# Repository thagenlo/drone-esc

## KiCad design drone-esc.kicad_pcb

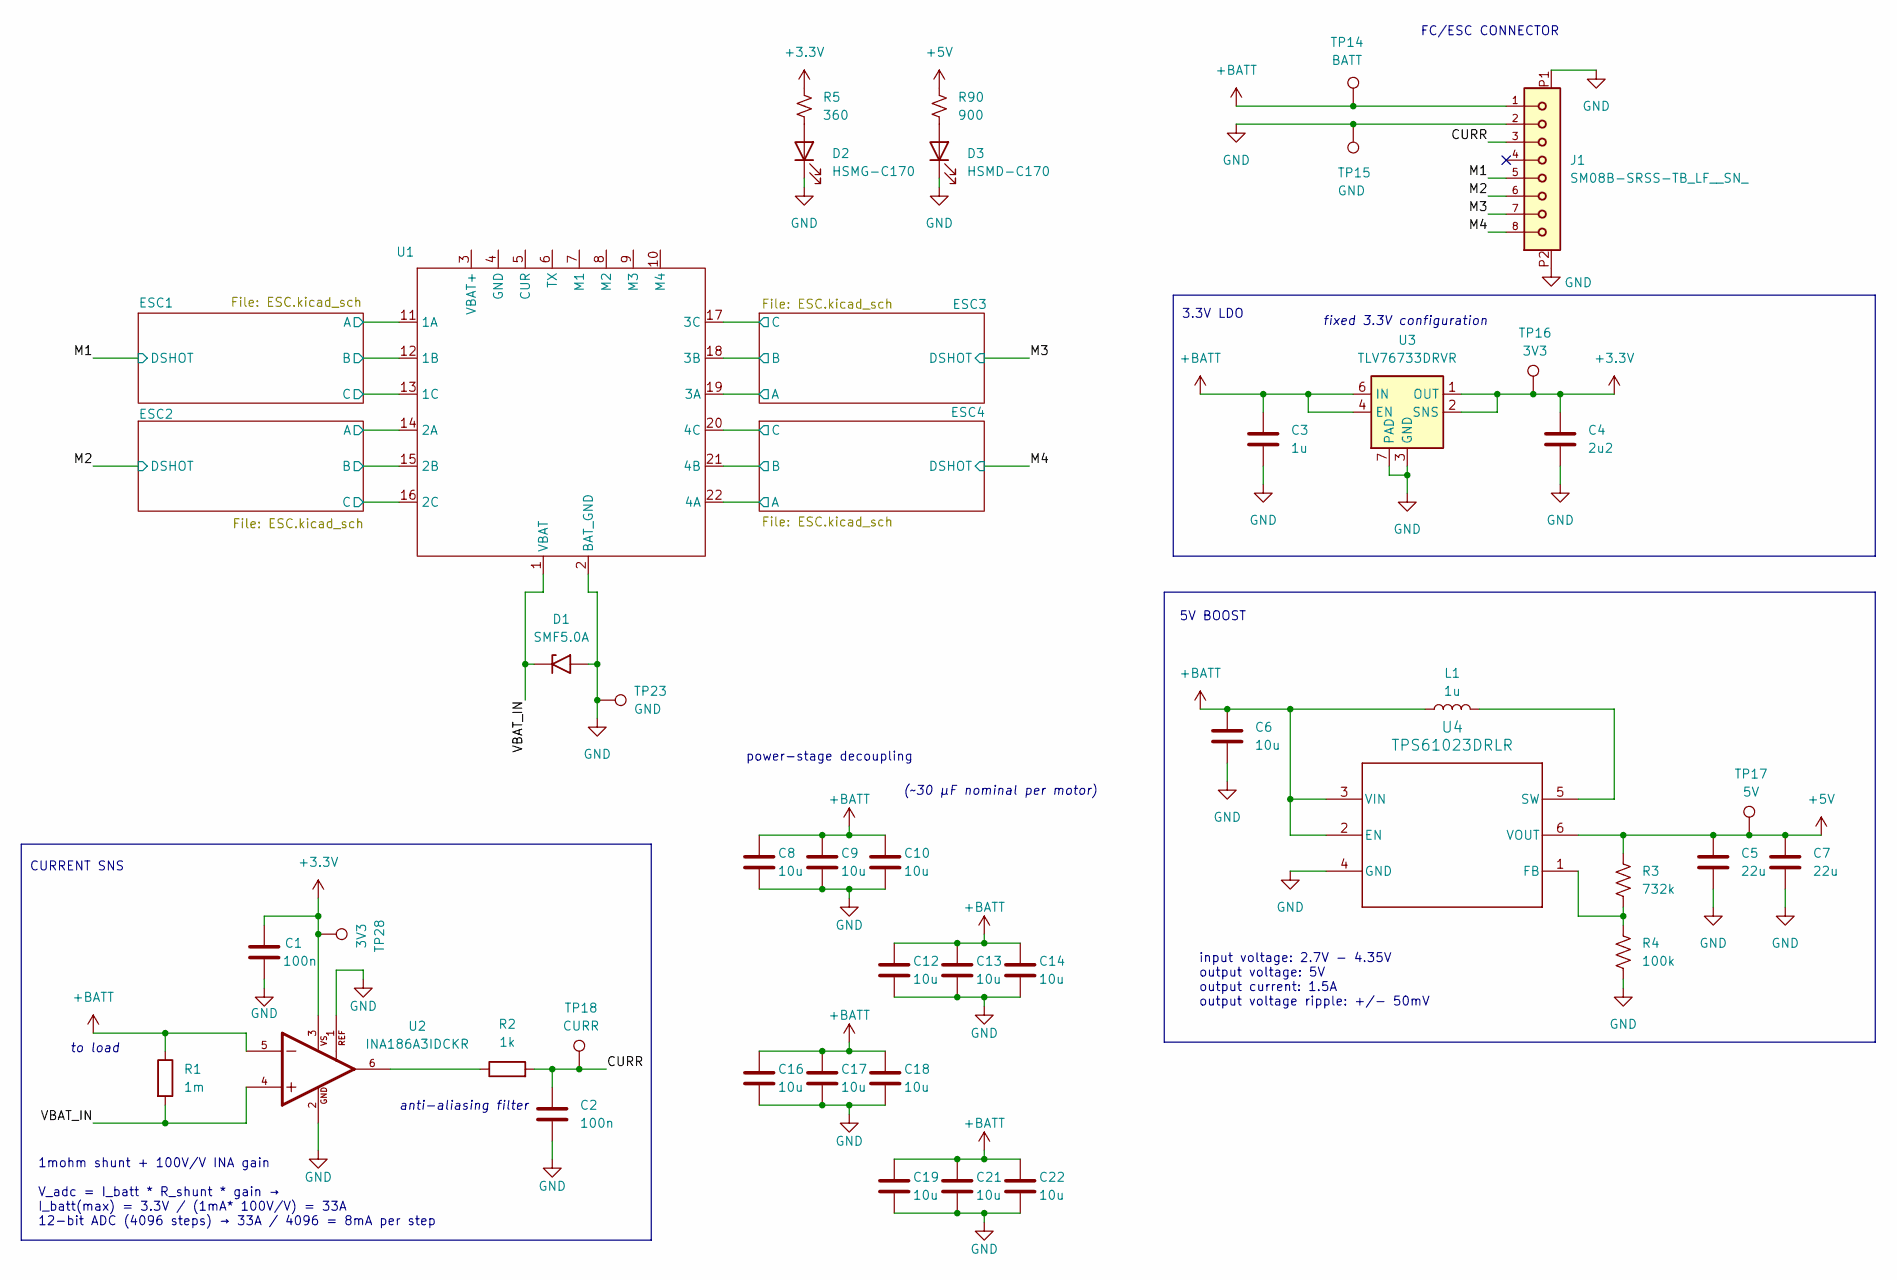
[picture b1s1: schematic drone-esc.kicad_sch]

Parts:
C1, C2: 100n; C_0201_0603Metric
C3: 1u; C_0201_0603Metric
C4: 2u2; C_0201_0603Metric
C5, C7: 22u; C_0201_0603Metric
C6: 10u; C_0201_0603Metric
C8, C9, C10, C12, C13, C14, C16, C17, C18, C19, C21, C22: 10u; C_0805_2012Metric
D1: SMF5.0A; D_SOD-123F
D2: HSMG-C170; LED_0805_2012Metric
D3: HSMD-C170; LED_0805_2012Metric
J1: SM08B-SRSS-TB_LF__SN_; JST_SM08B-SRSS-TB_LF__SN_
L1: 1u; L_0603_1608Metric
R1: 1m; R_2512_6332Metric
R2: 1k; R_0201_0603Metric
R3: 732k; R_0201_0603Metric
R4: 100k; R_0201_0603Metric
R5: 360; R_0201_0603Metric
R90: 900; R_0201_0603Metric
TP14: BATT; TestPoint_Pad_D1.0mm
TP15, TP23: GND; TestPoint_Pad_D1.0mm
TP16, TP28: 3V3; TestPoint_Pad_D1.0mm
TP17: 5V; TestPoint_Pad_D1.0mm
TP18: CURR; TestPoint_Pad_D1.0mm
U1: esc-board
U2: INA186A3IDCKR; SOT65P210X110-6N; PARTREV B
U3: TLV76733DRVR; WSON-6-1EP_2x2mm_P0.65mm_EP1x1.6mm_ThermalVias
U4: TPS61023DRLR; DRL0006A

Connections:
+3.3V: C1.1, C4.1, R5.1, TP16.1 (1_1), TP28.1, U2.3, U3.1 (OUT), U3.2 (SNS); also elsewhere on the board
+5V: C5.1, C7.1, R3.1, R90.1, TP17.1 (1_1), U4.6 (VOUT); also elsewhere on the board
+BATT: C3.1, C6.1, C8.1, C9.1, C10.1, C12.1, C13.1, C14.1, C16.1, C17.1, C18.1, C19.1, C21.1, C22.1, J1.1, L1.1, R1.1, TP14.1, U2.5, U3.4 (EN), U3.6 (IN), U4.2 (EN), U4.3 (VIN); also elsewhere on the board
/CURR: C2.1, J1.3, R2.2, TP18.1 (1_1)
/ESC1/MotorA: U1.11 (1A); also elsewhere on the board
/ESC1/MotorB: U1.12 (1B); also elsewhere on the board
/ESC1/MotorC: U1.13 (1C); also elsewhere on the board
/ESC2/MotorA: U1.14 (2A); also elsewhere on the board
/ESC2/MotorB: U1.15 (2B); also elsewhere on the board
/ESC2/MotorC: U1.16 (2C); also elsewhere on the board
/ESC3/MotorA: U1.19 (3A); also elsewhere on the board
/ESC3/MotorB: U1.18 (3B); also elsewhere on the board
/ESC3/MotorC: U1.17 (3C); also elsewhere on the board
/ESC4/MotorA: U1.22 (4A); also elsewhere on the board
/ESC4/MotorB: U1.21 (4B); also elsewhere on the board
/ESC4/MotorC: U1.20 (4C); also elsewhere on the board
/M1: J1.5; also elsewhere on the board
/M2: J1.6; also elsewhere on the board
/M3: J1.7; also elsewhere on the board
/M4: J1.8; also elsewhere on the board
/VBAT_IN: D1.1 (A1), R1.2, U1.1 (VBAT), U2.4
GND: C1.2, C2.2, C3.2, C4.2, C5.2, C6.2, C7.2, C8.2, C9.2, C10.2, C12.2, C13.2, C14.2, C16.2, C17.2, C18.2, C19.2, C21.2, C22.2, D1.2 (A2), D2.1 (K), D3.1 (K), J1.2, J1.P1, J1.P2, R4.2, TP15.1 (1_1), TP23.1, U1.2 (BAT_GND), U2.1, U2.2, U3.3 (GND), U3.5 (GND), U3.7 (PAD), U4.4 (GND); also elsewhere on the board
unnamed: D2.2 (A), R5.2
unnamed: D3.2 (A), R90.2
unnamed: R2.1, U2.6
unnamed: R3.2, R4.1, U4.1 (FB)
unnamed: L1.2, U4.5 (SW)

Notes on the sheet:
5V BOOST
(~30 µF nominal per motor)
fixed 3.3V configuration
1mohm shunt + 100V/V INA gain V_adc = I_batt * R_shunt * gain → I_batt(max) = 3.3V / (1mA* 100V/V) = 33A 12-bit ADC (4096 steps) → 33A / 4096 = 8mA per step
anti-aliasing filter
FC/ESC CONNECTOR
to load
3.3V LDO
power-stage decoupling
CURRENT SNS
input voltage: 2.7V - 4.35V output voltage: 5V output current: 1.5A output voltage ripple: +/- 50mV

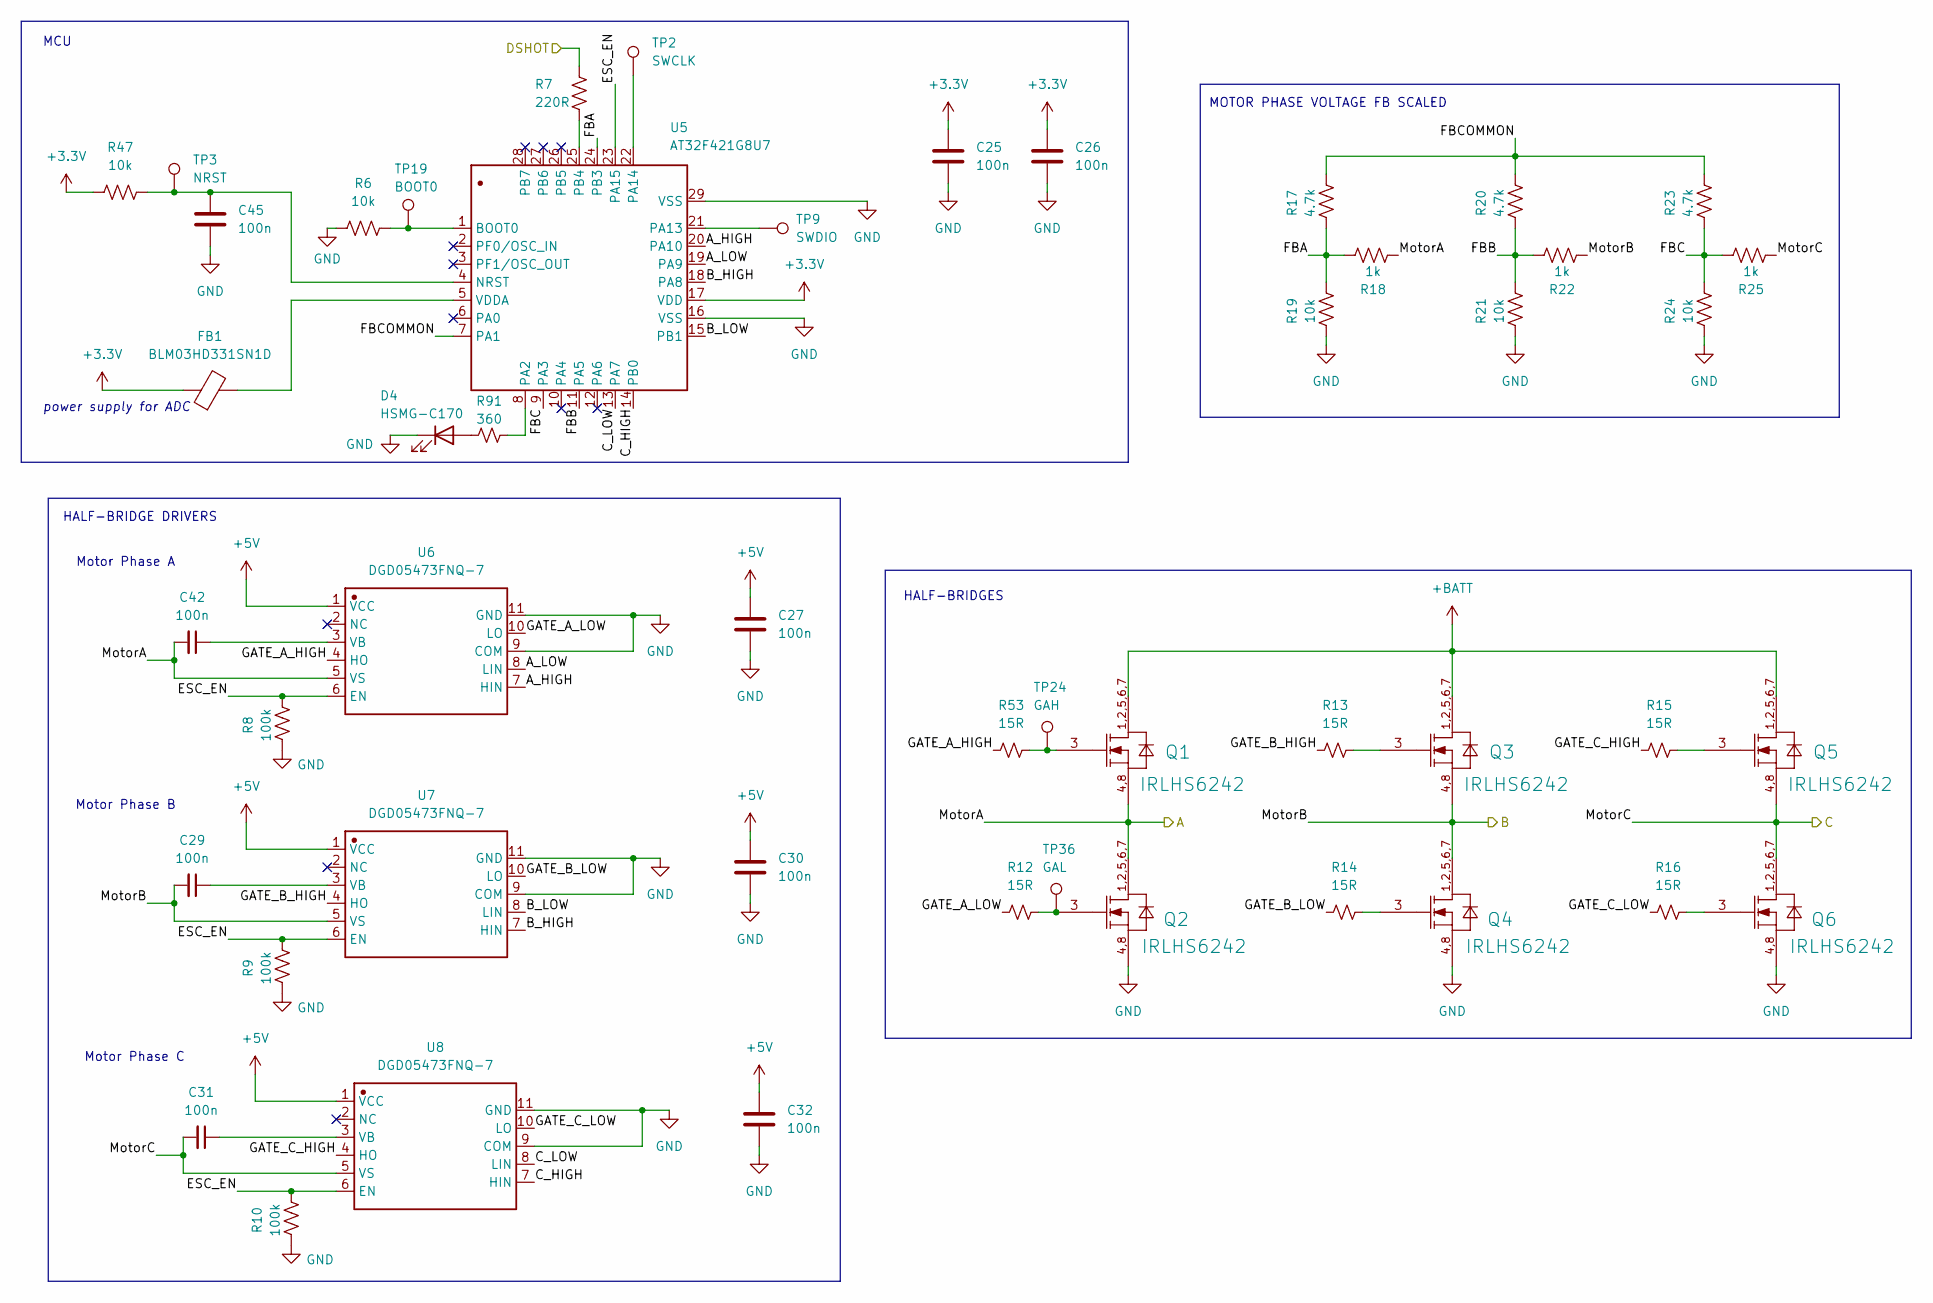
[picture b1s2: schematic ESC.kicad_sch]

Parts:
C25, C26, C27, C29, C30, C31, C32, C42, C45: 100n; C_0201_0603Metric
D4: HSMG-C170; LED_0805_2012Metric
FB1: BLM03HD331SN1D; R_0201_0603Metric
Q1, Q2, Q3, Q4, Q5, Q6: IRLHS6242; IRL100HS121-V
R6, R19, R21, R24, R47: 10k; R_0201_0603Metric
R7: 220R; R_0201_0603Metric
R8, R9, R10: 100k; R_0201_0603Metric
R12, R13, R14, R15, R16, R53: 15R; R_0201_0603Metric
R17, R20, R23: 4.7k; R_0201_0603Metric
R18, R22, R25: 1k; R_0201_0603Metric
R91: 360; R_0201_0603Metric
TP2: SWCLK; TestPoint_Pad_D1.0mm
TP3: NRST; TestPoint_Pad_D1.0mm
TP9: SWDIO; TestPoint_Pad_D1.0mm
TP19: BOOT0; TestPoint_Pad_D1.0mm
TP24: GAH; TestPoint_Pad_D1.0mm
TP36: GAL; TestPoint_Pad_D1.0mm
U5: AT32F421G8U7; QFN-28-1EP_4x4mm_P0.45mm_EP2.4x2.4mm; Manufacturer Part AT32F421G8U7
U6, U7, U8: DGD05473FNQ-7; DFN-10-1EP_3x3mm_P0.5mm_EP1.7x2.5mm; Manufacturer Part DGD05473FNQ-7

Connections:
+3.3V: C25.1, C26.1, FB1.1, R47.1, U5.17 (VDD); also elsewhere on the board
+5V: C27.1, C30.1, C32.1, U6.1 (VCC), U7.1 (VCC), U8.1 (VCC); also elsewhere on the board
+BATT: Q1.1 (DRAIN1), Q1.2 (DRAIN2), Q1.5 (DRAIN3), Q1.6 (DRAIN4), Q1.7 (DRAIN5), Q3.1 (DRAIN1), Q3.2 (DRAIN2), Q3.5 (DRAIN3), Q3.6 (DRAIN4), Q3.7 (DRAIN5), Q5.1 (DRAIN1), Q5.2 (DRAIN2), Q5.5 (DRAIN3), Q5.6 (DRAIN4), Q5.7 (DRAIN5); also elsewhere on the board
/ESC1/A_HIGH: U5.20 (PA10), U6.7 (HIN)
/ESC1/A_LOW: U5.19 (PA9), U6.8 (LIN)
/ESC1/B_HIGH: U5.18 (PA8), U7.7 (HIN)
/ESC1/B_LOW: U5.15 (PB1), U7.8 (LIN)
/ESC1/C_HIGH: U5.14 (PB0), U8.7 (HIN)
/ESC1/C_LOW: U5.13 (PA7), U8.8 (LIN)
/ESC1/ESC_EN: R8.1, R9.1, R10.1, U5.23 (PA15), U6.6 (EN), U7.6 (EN), U8.6 (EN)
/ESC1/FBA: R17.2, R18.1, R19.1, U5.24 (PB3)
/ESC1/FBB: R20.2, R21.1, R22.1, U5.11 (PA5)
/ESC1/FBC: R23.2, R24.1, R25.1, U5.9 (PA3)
/ESC1/FBCOMMON: R17.1, R20.1, R23.1, U5.7 (PA1)
/ESC1/GATE_A_HIGH: R53.1, U6.4 (HO)
/ESC1/GATE_A_LOW: R12.1, U6.10 (LO)
/ESC1/GATE_B_HIGH: R13.1, U7.4 (HO)
/ESC1/GATE_B_LOW: R14.1, U7.10 (LO)
/ESC1/GATE_C_HIGH: R15.1, U8.4 (HO)
/ESC1/GATE_C_LOW: R16.1, U8.10 (LO)
/ESC1/MotorA: C42.2, Q1.4 (SOURCE1), Q1.8 (SOURCE2), Q2.1 (DRAIN1), Q2.2 (DRAIN2), Q2.5 (DRAIN3), Q2.6 (DRAIN4), Q2.7 (DRAIN5), R18.2, U6.5 (VS); also elsewhere on the board
/ESC1/MotorB: C29.2, Q3.4 (SOURCE1), Q3.8 (SOURCE2), Q4.1 (DRAIN1), Q4.2 (DRAIN2), Q4.5 (DRAIN3), Q4.6 (DRAIN4), Q4.7 (DRAIN5), R22.2, U7.5 (VS); also elsewhere on the board
/ESC1/MotorC: C31.2, Q5.4 (SOURCE1), Q5.8 (SOURCE2), Q6.1 (DRAIN1), Q6.2 (DRAIN2), Q6.5 (DRAIN3), Q6.6 (DRAIN4), Q6.7 (DRAIN5), R25.2, U8.5 (VS); also elsewhere on the board
/M1: R7.2; also elsewhere on the board
GND: C25.2, C26.2, C27.2, C30.2, C32.2, C45.2, D4.1 (K), Q2.4 (SOURCE1), Q2.8 (SOURCE2), Q4.4 (SOURCE1), Q4.8 (SOURCE2), Q6.4 (SOURCE1), Q6.8 (SOURCE2), R6.1, R8.2, R9.2, R10.2, R19.2, R21.2, R24.2, U5.16 (VSS), U5.29 (VSS), U6.9 (COM), U6.11 (GND), U7.9 (COM), U7.11 (GND), U8.9 (COM), U8.11 (GND); also elsewhere on the board
unnamed: D4.2 (A), R91.2
unnamed: Q1.3 (GATE), R53.2
unnamed: Q2.3 (GATE), R12.2
unnamed: Q3.3 (GATE), R13.2
unnamed: Q4.3 (GATE), R14.2
unnamed: Q5.3 (GATE), R15.2
unnamed: Q6.3 (GATE), R16.2
unnamed: R6.2, U5.1 (BOOT0)
unnamed: C45.1, R47.2, U5.4 (NRST)
unnamed: R7.1, U5.25 (PB4)
unnamed: FB1.2, U5.5 (VDDA)
unnamed: C42.1, U6.3 (VB)
unnamed: C29.1, U7.3 (VB)
unnamed: C31.1, U8.3 (VB)

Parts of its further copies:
C28, C33, C34, C35, C36, C37, C38, C39, C40, C41, C43, C44, C46, C47, C48, C49, C50, C51, C52, C53, C54, C55, C56, C57, C58, C59, C60: 100n; C_0201_0603Metric
FB2, FB3, FB4: BLM03HD331SN1D; R_0201_0603Metric
Q7, Q8, Q9, Q10, Q11, Q12, Q13, Q14, Q15, Q16, Q17, Q18, Q19, Q20, Q21, Q22, Q23, Q24: IRLHS6242; IRL100HS121-V
R11, R27, R28, R29, R49, R50, R70, R71, R72: 100k; R_0201_0603Metric
R26, R30, R35, R40, R45, R48, R51, R57, R62, R67, R69, R73, R78, R83, R88: 10k; R_0201_0603Metric
R31, R52, R74: 220R; R_0201_0603Metric
R32, R33, R36, R37, R42, R43, R54, R55, R58, R59, R64, R65, R75, R76, R79, R80, R85, R86: 15R; R_0201_0603Metric
R34, R39, R44, R56, R61, R66, R77, R82, R87: 4.7k; R_0201_0603Metric
R38, R41, R46, R60, R63, R68, R81, R84, R89: 1k; R_0201_0603Metric
U9, U10, U11, U13, U14, U15, U17, U18, U19: DGD05473FNQ-7; DFN-10-1EP_3x3mm_P0.5mm_EP1.7x2.5mm; Manufacturer Part DGD05473FNQ-7
U12, U16, U20: AT32F421G8U7; QFN-28-1EP_4x4mm_P0.45mm_EP2.4x2.4mm; Manufacturer Part AT32F421G8U7

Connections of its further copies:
+3.3V: C40.1, C41.1, C50.1, C51.1, C59.1, C60.1, FB2.1, FB3.1, FB4.1, R26.1, R48.1, R69.1, U12.17 (VDD), U16.17 (VDD), U20.17 (VDD); also elsewhere on the board
+5V: C28.1, C37.1, C38.1, C39.1, C48.1, C49.1, C56.1, C57.1, C58.1, U9.1 (VCC), U10.1 (VCC), U11.1 (VCC), U13.1 (VCC), U14.1 (VCC), U15.1 (VCC), U17.1 (VCC), U18.1 (VCC), U19.1 (VCC); also elsewhere on the board
+BATT: Q7.1 (DRAIN1), Q7.2 (DRAIN2), Q7.5 (DRAIN3), Q7.6 (DRAIN4), Q7.7 (DRAIN5), Q9.1 (DRAIN1), Q9.2 (DRAIN2), Q9.5 (DRAIN3), Q9.6 (DRAIN4), Q9.7 (DRAIN5), Q11.1 (DRAIN1), Q11.2 (DRAIN2), Q11.5 (DRAIN3), Q11.6 (DRAIN4), Q11.7 (DRAIN5), Q13.1 (DRAIN1), Q13.2 (DRAIN2), Q13.5 (DRAIN3), Q13.6 (DRAIN4), Q13.7 (DRAIN5), Q15.1 (DRAIN1), Q15.2 (DRAIN2), Q15.5 (DRAIN3), Q15.6 (DRAIN4), Q15.7 (DRAIN5), Q17.1 (DRAIN1), Q17.2 (DRAIN2), Q17.5 (DRAIN3), Q17.6 (DRAIN4), Q17.7 (DRAIN5), Q19.1 (DRAIN1), Q19.2 (DRAIN2), Q19.5 (DRAIN3), Q19.6 (DRAIN4), Q19.7 (DRAIN5), Q21.1 (DRAIN1), Q21.2 (DRAIN2), Q21.5 (DRAIN3), Q21.6 (DRAIN4), Q21.7 (DRAIN5), Q23.1 (DRAIN1), Q23.2 (DRAIN2), Q23.5 (DRAIN3), Q23.6 (DRAIN4), Q23.7 (DRAIN5); also elsewhere on the board
/ESC2/A_HIGH: U9.7 (HIN), U12.20 (PA10)
/ESC2/A_LOW: U9.8 (LIN), U12.19 (PA9)
/ESC2/B_HIGH: U10.7 (HIN), U12.18 (PA8)
/ESC2/B_LOW: U10.8 (LIN), U12.15 (PB1)
/ESC2/C_HIGH: U11.7 (HIN), U12.14 (PB0)
/ESC2/C_LOW: U11.8 (LIN), U12.13 (PA7)
/ESC2/ESC_EN: R27.1, R28.1, R29.1, U9.6 (EN), U10.6 (EN), U11.6 (EN), U12.23 (PA15)
/ESC2/FBA: R34.2, R35.1, R38.1, U12.24 (PB3)
/ESC2/FBB: R39.2, R40.1, R41.1, U12.11 (PA5)
/ESC2/FBC: R44.2, R45.1, R46.1, U12.9 (PA3)
/ESC2/FBCOMMON: R34.1, R39.1, R44.1, U12.7 (PA1)
/ESC2/GATE_A_HIGH: R32.1, U9.4 (HO)
/ESC2/GATE_A_LOW: R33.1, U9.10 (LO)
/ESC2/GATE_B_HIGH: R36.1, U10.4 (HO)
/ESC2/GATE_B_LOW: R37.1, U10.10 (LO)
/ESC2/GATE_C_HIGH: R42.1, U11.4 (HO)
/ESC2/GATE_C_LOW: R43.1, U11.10 (LO)
/ESC2/MotorA: C33.2, Q7.4 (SOURCE1), Q7.8 (SOURCE2), Q8.1 (DRAIN1), Q8.2 (DRAIN2), Q8.5 (DRAIN3), Q8.6 (DRAIN4), Q8.7 (DRAIN5), R38.2, U9.5 (VS); also elsewhere on the board
/ESC2/MotorB: C34.2, Q9.4 (SOURCE1), Q9.8 (SOURCE2), Q10.1 (DRAIN1), Q10.2 (DRAIN2), Q10.5 (DRAIN3), Q10.6 (DRAIN4), Q10.7 (DRAIN5), R41.2, U10.5 (VS); also elsewhere on the board
/ESC2/MotorC: C35.2, Q11.4 (SOURCE1), Q11.8 (SOURCE2), Q12.1 (DRAIN1), Q12.2 (DRAIN2), Q12.5 (DRAIN3), Q12.6 (DRAIN4), Q12.7 (DRAIN5), R46.2, U11.5 (VS); also elsewhere on the board
/ESC3/A_HIGH: U13.7 (HIN), U16.20 (PA10)
/ESC3/A_LOW: U13.8 (LIN), U16.19 (PA9)
/ESC3/B_HIGH: U14.7 (HIN), U16.18 (PA8)
/ESC3/B_LOW: U14.8 (LIN), U16.15 (PB1)
/ESC3/C_HIGH: U15.7 (HIN), U16.14 (PB0)
/ESC3/C_LOW: U15.8 (LIN), U16.13 (PA7)
/ESC3/ESC_EN: R11.1, R49.1, R50.1, U13.6 (EN), U14.6 (EN), U15.6 (EN), U16.23 (PA15)
/ESC3/FBA: R56.2, R57.1, R60.1, U16.24 (PB3)
/ESC3/FBB: R61.2, R62.1, R63.1, U16.11 (PA5)
/ESC3/FBC: R66.2, R67.1, R68.1, U16.9 (PA3)
/ESC3/FBCOMMON: R56.1, R61.1, R66.1, U16.7 (PA1)
/ESC3/GATE_A_HIGH: R54.1, U13.4 (HO)
/ESC3/GATE_A_LOW: R55.1, U13.10 (LO)
/ESC3/GATE_B_HIGH: R58.1, U14.4 (HO)
/ESC3/GATE_B_LOW: R59.1, U14.10 (LO)
/ESC3/GATE_C_HIGH: R64.1, U15.4 (HO)
/ESC3/GATE_C_LOW: R65.1, U15.10 (LO)
/ESC3/MotorA: C43.2, Q13.4 (SOURCE1), Q13.8 (SOURCE2), Q14.1 (DRAIN1), Q14.2 (DRAIN2), Q14.5 (DRAIN3), Q14.6 (DRAIN4), Q14.7 (DRAIN5), R60.2, U13.5 (VS); also elsewhere on the board
/ESC3/MotorB: C44.2, Q15.4 (SOURCE1), Q15.8 (SOURCE2), Q16.1 (DRAIN1), Q16.2 (DRAIN2), Q16.5 (DRAIN3), Q16.6 (DRAIN4), Q16.7 (DRAIN5), R63.2, U14.5 (VS); also elsewhere on the board
/ESC3/MotorC: C46.2, Q17.4 (SOURCE1), Q17.8 (SOURCE2), Q18.1 (DRAIN1), Q18.2 (DRAIN2), Q18.5 (DRAIN3), Q18.6 (DRAIN4), Q18.7 (DRAIN5), R68.2, U15.5 (VS); also elsewhere on the board
/ESC4/A_HIGH: U17.7 (HIN), U20.20 (PA10)
/ESC4/A_LOW: U17.8 (LIN), U20.19 (PA9)
/ESC4/B_HIGH: U18.7 (HIN), U20.18 (PA8)
/ESC4/B_LOW: U18.8 (LIN), U20.15 (PB1)
/ESC4/C_HIGH: U19.7 (HIN), U20.14 (PB0)
/ESC4/C_LOW: U19.8 (LIN), U20.13 (PA7)
/ESC4/ESC_EN: R70.1, R71.1, R72.1, U17.6 (EN), U18.6 (EN), U19.6 (EN), U20.23 (PA15)
/ESC4/FBA: R77.2, R78.1, R81.1, U20.24 (PB3)
/ESC4/FBB: R82.2, R83.1, R84.1, U20.11 (PA5)
/ESC4/FBC: R87.2, R88.1, R89.1, U20.9 (PA3)
/ESC4/FBCOMMON: R77.1, R82.1, R87.1, U20.7 (PA1)
/ESC4/GATE_A_HIGH: R75.1, U17.4 (HO)
/ESC4/GATE_A_LOW: R76.1, U17.10 (LO)
/ESC4/GATE_B_HIGH: R79.1, U18.4 (HO)
/ESC4/GATE_B_LOW: R80.1, U18.10 (LO)
/ESC4/GATE_C_HIGH: R85.1, U19.4 (HO)
/ESC4/GATE_C_LOW: R86.1, U19.10 (LO)
/ESC4/MotorA: C52.2, Q19.4 (SOURCE1), Q19.8 (SOURCE2), Q20.1 (DRAIN1), Q20.2 (DRAIN2), Q20.5 (DRAIN3), Q20.6 (DRAIN4), Q20.7 (DRAIN5), R81.2, U17.5 (VS); also elsewhere on the board
/ESC4/MotorB: C53.2, Q21.4 (SOURCE1), Q21.8 (SOURCE2), Q22.1 (DRAIN1), Q22.2 (DRAIN2), Q22.5 (DRAIN3), Q22.6 (DRAIN4), Q22.7 (DRAIN5), R84.2, U18.5 (VS); also elsewhere on the board
/ESC4/MotorC: C54.2, Q23.4 (SOURCE1), Q23.8 (SOURCE2), Q24.1 (DRAIN1), Q24.2 (DRAIN2), Q24.5 (DRAIN3), Q24.6 (DRAIN4), Q24.7 (DRAIN5), R89.2, U19.5 (VS); also elsewhere on the board
/M2: R31.2; also elsewhere on the board
/M3: R52.2; also elsewhere on the board
/M4: R74.2; also elsewhere on the board
GND: C28.2, C36.2, C37.2, C38.2, C39.2, C40.2, C41.2, C47.2, C48.2, C49.2, C50.2, C51.2, C55.2, C56.2, C57.2, C58.2, C59.2, C60.2, Q8.4 (SOURCE1), Q8.8 (SOURCE2), Q10.4 (SOURCE1), Q10.8 (SOURCE2), Q12.4 (SOURCE1), Q12.8 (SOURCE2), Q14.4 (SOURCE1), Q14.8 (SOURCE2), Q16.4 (SOURCE1), Q16.8 (SOURCE2), Q18.4 (SOURCE1), Q18.8 (SOURCE2), Q20.4 (SOURCE1), Q20.8 (SOURCE2), Q22.4 (SOURCE1), Q22.8 (SOURCE2), Q24.4 (SOURCE1), Q24.8 (SOURCE2), R11.2, R27.2, R28.2, R29.2, R30.1, R35.2, R40.2, R45.2, R49.2, R50.2, R51.1, R57.2, R62.2, R67.2, R70.2, R71.2, R72.2, R73.1, R78.2, R83.2, R88.2, U9.9 (COM), U9.11 (GND), U10.9 (COM), U10.11 (GND), U11.9 (COM), U11.11 (GND), U12.16 (VSS), U12.29 (VSS), U13.9 (COM), U13.11 (GND), U14.9 (COM), U14.11 (GND), U15.9 (COM), U15.11 (GND), U16.16 (VSS), U16.29 (VSS), U17.9 (COM), U17.11 (GND), U18.9 (COM), U18.11 (GND), U19.9 (COM), U19.11 (GND), U20.16 (VSS), U20.29 (VSS); also elsewhere on the board
unnamed: Q7.3 (GATE), R32.2
unnamed: Q8.3 (GATE), R33.2
unnamed: Q9.3 (GATE), R36.2
unnamed: Q10.3 (GATE), R37.2
unnamed: Q11.3 (GATE), R42.2
unnamed: Q12.3 (GATE), R43.2
unnamed: Q13.3 (GATE), R54.2
unnamed: Q14.3 (GATE), R55.2
unnamed: Q15.3 (GATE), R58.2
unnamed: Q16.3 (GATE), R59.2
unnamed: Q17.3 (GATE), R64.2
unnamed: Q18.3 (GATE), R65.2
unnamed: Q19.3 (GATE), R75.2
unnamed: Q20.3 (GATE), R76.2
unnamed: Q21.3 (GATE), R79.2
unnamed: Q22.3 (GATE), R80.2
unnamed: Q23.3 (GATE), R85.2
unnamed: Q24.3 (GATE), R86.2
unnamed: C33.1, U9.3 (VB)
unnamed: C34.1, U10.3 (VB)
unnamed: C35.1, U11.3 (VB)
unnamed: R30.2, U12.1 (BOOT0)
unnamed: C36.1, R26.2, U12.4 (NRST)
unnamed: R31.1, U12.25 (PB4)
unnamed: FB2.2, U12.5 (VDDA)
unnamed: C43.1, U13.3 (VB)
unnamed: C44.1, U14.3 (VB)
unnamed: C46.1, U15.3 (VB)
unnamed: R51.2, U16.1 (BOOT0)
unnamed: C47.1, R48.2, U16.4 (NRST)
unnamed: R52.1, U16.25 (PB4)
unnamed: FB3.2, U16.5 (VDDA)
unnamed: C52.1, U17.3 (VB)
unnamed: C53.1, U18.3 (VB)
unnamed: C54.1, U19.3 (VB)
unnamed: R73.2, U20.1 (BOOT0)
unnamed: C55.1, R69.2, U20.4 (NRST)
unnamed: R74.1, U20.25 (PB4)
unnamed: FB4.2, U20.5 (VDDA)

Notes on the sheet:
power supply for ADC
Motor Phase C
HALF-BRIDGES
MCU
HALF-BRIDGE DRIVERS
Motor Phase B
MOTOR PHASE VOLTAGE FB SCALED
Motor Phase A

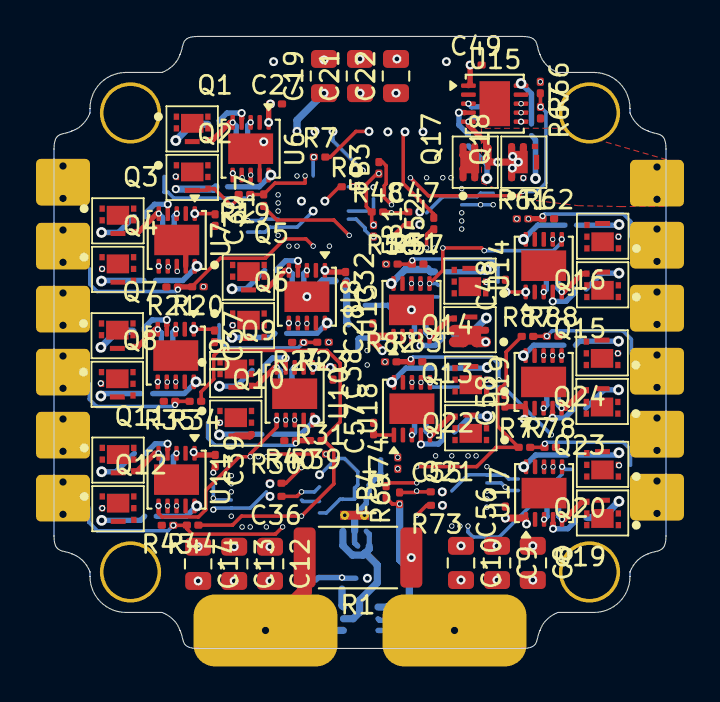
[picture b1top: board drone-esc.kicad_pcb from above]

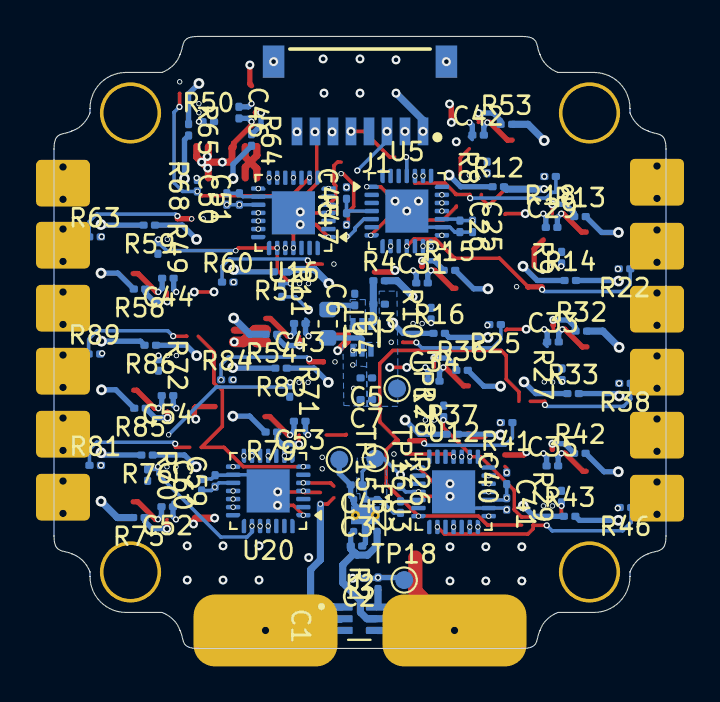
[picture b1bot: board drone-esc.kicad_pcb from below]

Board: 6 copper layers, 34.0 x 34.0 mm, 194 parts (95 on the bottom side), 145 nets.

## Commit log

2026-04-27 added board footprint
2026-04-27 basic placement 1
2026-04-27 placement 2 (starting routing)
2026-04-27 placement of power
2026-04-27 esc1 place and route
2026-04-27 duplicate layout and group
2026-04-27 final final group and place
2026-04-28 good placement 1
2026-04-28 place2
2026-04-28 duplicate layout+ place
2026-04-28 4/28 - 6:20PM
2026-04-29 4:24pm 4/29
2026-04-29 routed power
2026-04-29 half placed
2026-04-29 main placing
2026-04-29 something
2026-04-30 routed motor 1
2026-04-30 routed motor 2
2026-04-30 routed motor 3
2026-04-30 routed motor 4
2026-04-30 routed boost converted
2026-04-30 routed ldo and ina
2026-04-30 finish before power
2026-04-30 +3.3V power plane
2026-04-30 routed +5V
2026-04-30 lastest
